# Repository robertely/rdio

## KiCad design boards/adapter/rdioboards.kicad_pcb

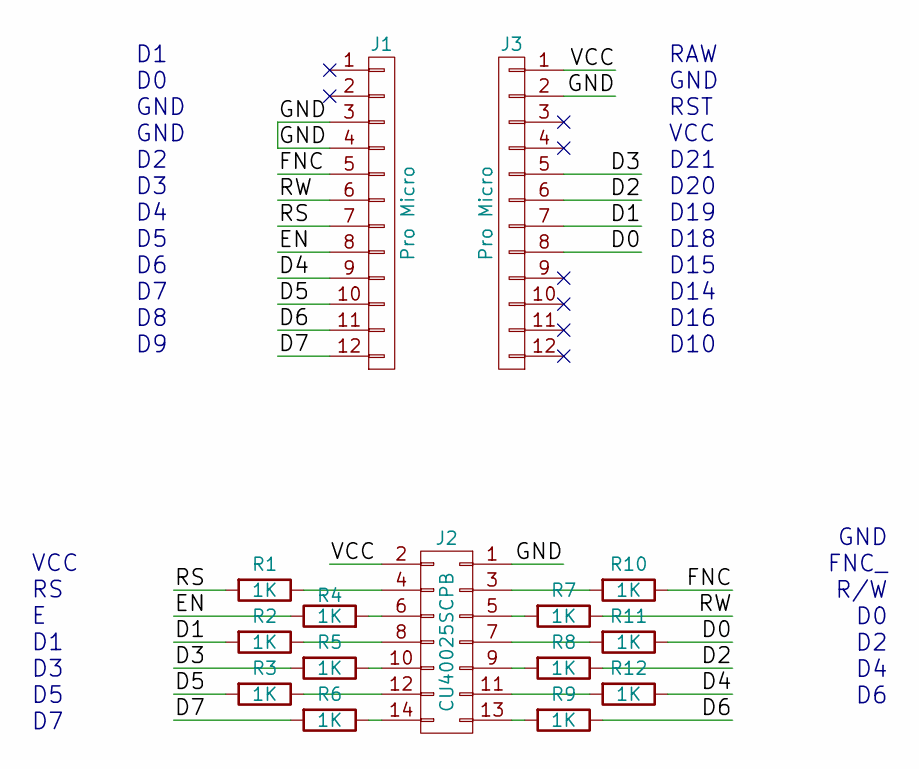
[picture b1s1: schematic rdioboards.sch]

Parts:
J1, J3: Pro Micro; Pin_Header_Straight_1x12_Pitch2.54mm
J2: CU40025SCPB; Pin_Header_Straight_2x07_Pitch2.54mm
R1, R2, R3, R4, R5, R6, R7, R8, R9, R10, R11, R12: 1K; R_1206_HandSoldering

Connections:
/D0: J3.8, R11.1
/D1: J3.7, R2.2
/D2: J3.6, R8.1
/D3: J3.5, R5.2
/D4: J1.9, R12.1
/D5: J1.10, R3.2
/D6: J1.11, R9.1
/D7: J1.12, R6.2
/EN: J1.8, R4.1
/FNC: J1.5, R10.1
/GND: J1.3, J1.4, J2.1, J3.2
/RS: J1.7, R1.2
/RW: J1.6, R7.1
/VCC: J2.2, J3.1
unnamed: J2.3, R10.2
unnamed: J2.4, R1.1
unnamed: J2.5, R7.2
unnamed: J2.6, R4.2
unnamed: J2.7, R11.2
unnamed: J2.8, R2.1
unnamed: J2.9, R8.2
unnamed: J2.10, R5.1
unnamed: J2.11, R12.2
unnamed: J2.12, R3.1
unnamed: J2.13, R9.2
unnamed: J2.14, R6.1

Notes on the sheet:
D1 D0 GND GND D2 D3 D4 D5 D6 D7 D8 D9
RAW GND RST VCC D21 D20 D19 D18 D15 D14 D16 D10
GND FNC_ R/W D0 D2 D4 D6
VCC RS E D1 D3 D5 D7

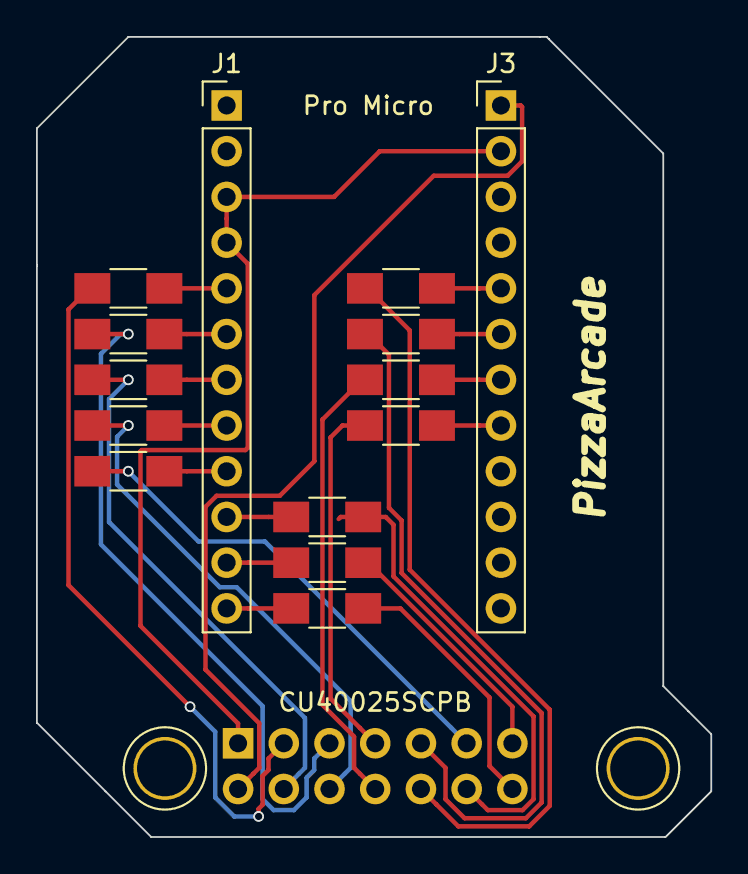
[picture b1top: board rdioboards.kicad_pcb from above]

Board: 2 copper layers, 37.5 x 44.5 mm, 15 parts (1 on the bottom side), 26 nets.

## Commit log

2017-10-24 init
2018-03-04 things
2018-03-04 stuff
2018-03-13 toml
2018-03-16 reorg, start on daemon
2018-03-19 derps
